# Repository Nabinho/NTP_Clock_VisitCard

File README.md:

# NTP_Clock_VisitCard

Linkit 7697 based NTP Digital Clock with a Visti Card PCB

I have the idea of creating an Visit Card to promote myself as a Software and Hardware Developer and project consultant, and for that I decided to go with a PCB in the format of a Credit Card. The circuit chosen is a project I always wanted to build, as I don´t have clocks due to the time to time need for manual calibration. So I connected the LinkIt 7697 (unfortunately discontinued) I had available, to connect it to a NTP server, and be always up to time. The board then controls 4 7-digits displays by 4 4511 ICs that are indirectly driven by ULN2003 transistors.

If you are interested in building your own Visit Card based on this project, feel free to change the PCB file with your own information. Just remember to give some credit.

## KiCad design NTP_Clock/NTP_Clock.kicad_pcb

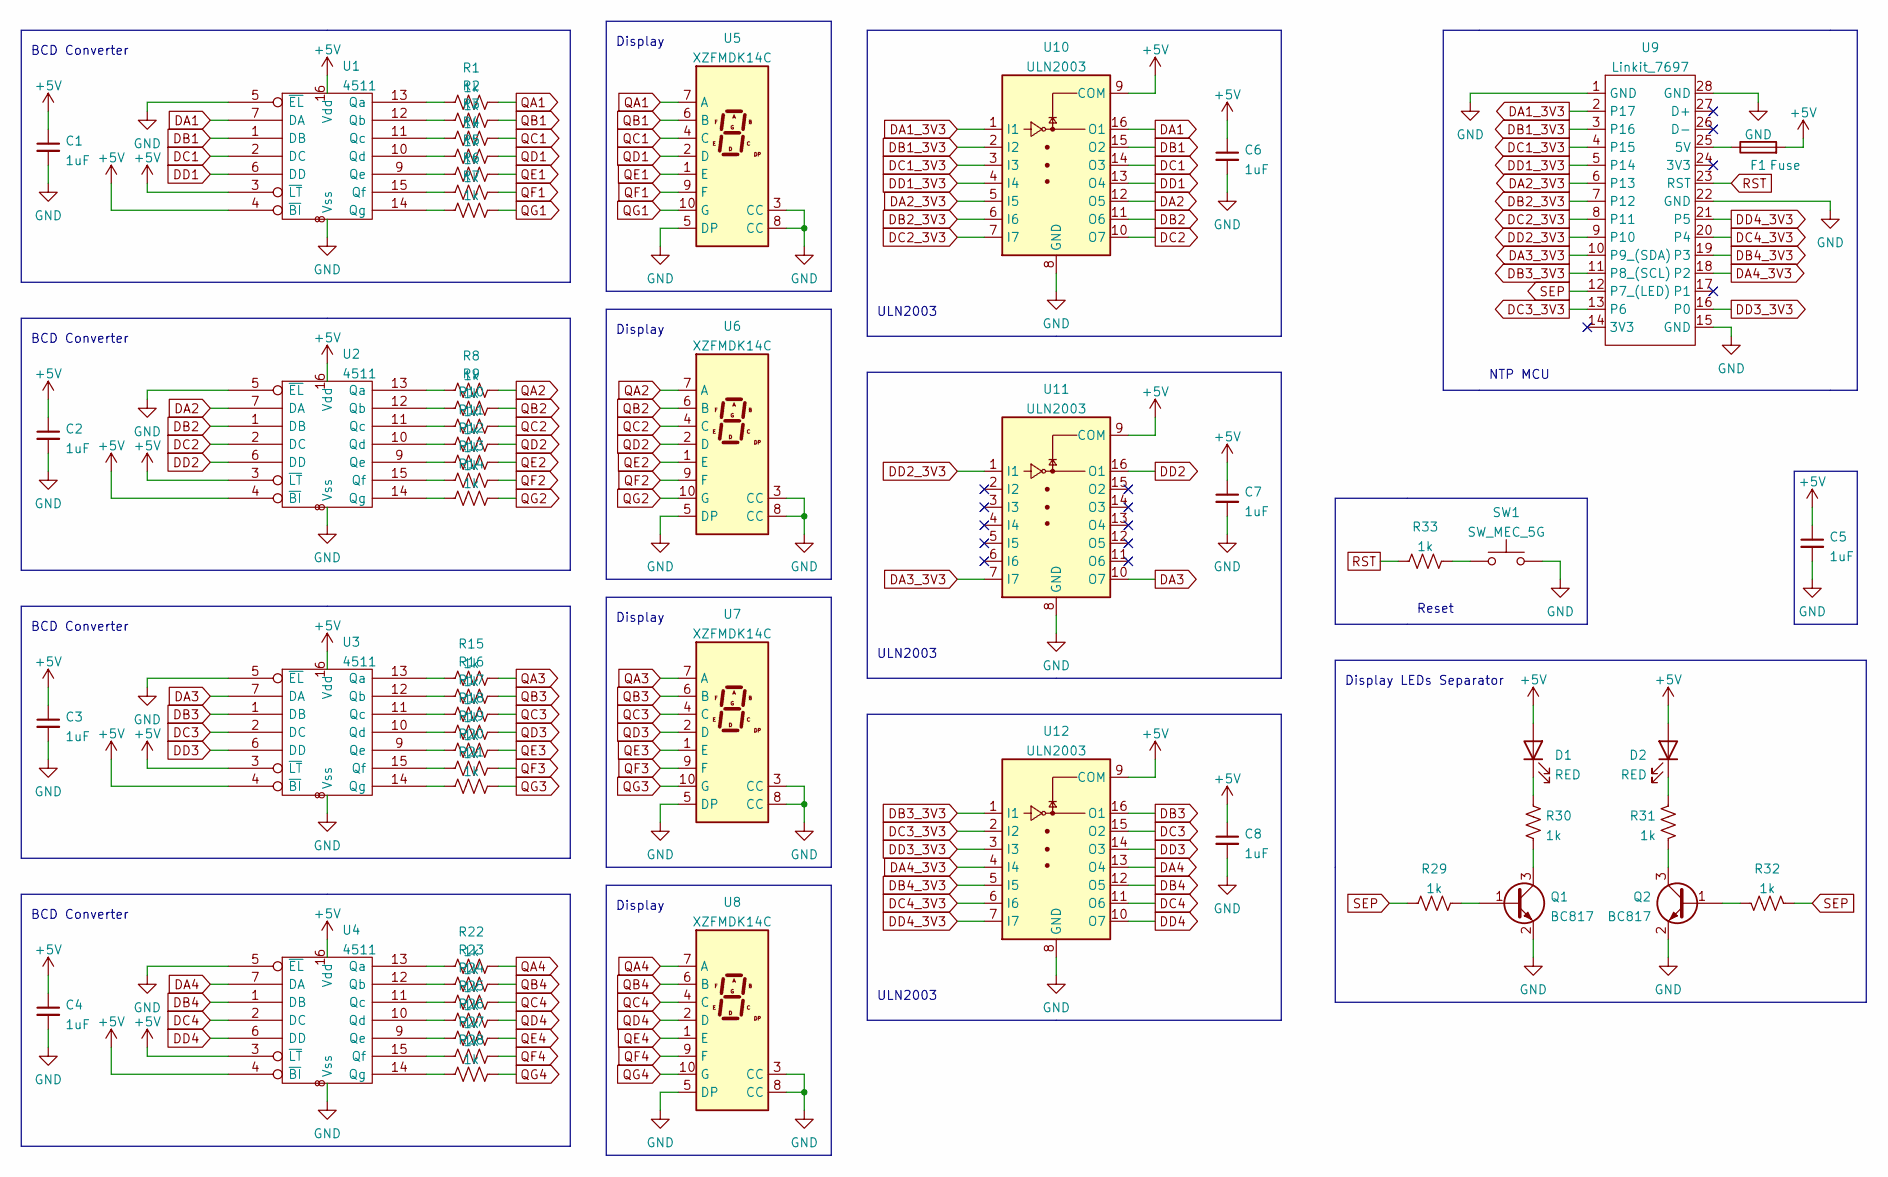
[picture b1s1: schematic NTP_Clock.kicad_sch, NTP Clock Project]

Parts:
C1, C2, C3, C4, C5, C6, C7, C8: 1uF; C_0805_2012Metric
D1, D2: RED; LED_0805_2012Metric
F1: Fuse; Fuse_0805_2012Metric
Q1, Q2: BC817; SOT-23
R1, R2, R3, R4, R5, R6, R7, R8, R9, R10, R11, R12, R13, R14, R15, R16, R17, R18, R19, R20, R21, R22, R23, R24, R25, R26, R27, R28, R29, R30, R31, R32, R33: 1k; R_0805_2012Metric
SW1: SW_MEC_5G; SW_SPST_SKQG_WithStem
U1, U2, U3, U4: 4511; SO-16_5.3x10.2mm_P1.27mm
U5, U6, U7, U8: XZFMDK14C; 7SEGMENT-LED__HDSM531_HDSM533_SMD
U9: Linkit_7697; Linkit
U10, U11, U12: ULN2003; SO-16_5.3x10.2mm_P1.27mm

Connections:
+5V: C1.1, C2.1, C3.1, C4.1, C5.1, C6.1, C7.1, C8.1, D1.2 (A), D2.2 (A), F1.2, U1.3 (~LT), U1.4 (~BI), U1.16 (Vdd), U2.3 (~LT), U2.4 (~BI), U2.16 (Vdd), U3.3 (~LT), U3.4 (~BI), U3.16 (Vdd), U4.3 (~LT), U4.4 (~BI), U4.16 (Vdd), U10.9 (COM), U11.9 (COM), U12.9 (COM)
DA1: U1.7 (DA), U10.16 (O1)
DA1_3V3: U9.2 (P17), U10.1 (I1)
DA2: U2.7 (DA), U10.12 (O5)
DA2_3V3: U9.6 (P13), U10.5 (I5)
DA3: U3.7 (DA), U11.10 (O7)
DA3_3V3: U9.10 (P9_(SDA)), U11.7 (I7)
DA4: U4.7 (DA), U12.13 (O4)
DA4_3V3: U9.18 (P2), U12.4 (I4)
DB1: U1.1 (DB), U10.15 (O2)
DB1_3V3: U9.3 (P16), U10.2 (I2)
DB2: U2.1 (DB), U10.11 (O6)
DB2_3V3: U9.7 (P12), U10.6 (I6)
DB3: U3.1 (DB), U12.16 (O1)
DB3_3V3: U9.11 (P8_(SCL)), U12.1 (I1)
DB4: U4.1 (DB), U12.12 (O5)
DB4_3V3: U9.19 (P3), U12.5 (I5)
DC1: U1.2 (DC), U10.14 (O3)
DC1_3V3: U9.4 (P15), U10.3 (I3)
DC2: U2.2 (DC), U10.10 (O7)
DC2_3V3: U9.8 (P11), U10.7 (I7)
DC3: U3.2 (DC), U12.15 (O2)
DC3_3V3: U9.13 (P6), U12.2 (I2)
DC4: U4.2 (DC), U12.11 (O6)
DC4_3V3: U9.20 (P4), U12.6 (I6)
DD1: U1.6 (DD), U10.13 (O4)
DD1_3V3: U9.5 (P14), U10.4 (I4)
DD2: U2.6 (DD), U11.16 (O1)
DD2_3V3: U9.9 (P10), U11.1 (I1)
DD3: U3.6 (DD), U12.14 (O3)
DD3_3V3: U9.16 (P0), U12.3 (I3)
DD4: U4.6 (DD), U12.10 (O7)
DD4_3V3: U9.21 (P5), U12.7 (I7)
unnamed: D1.1 (K), R30.2
unnamed: D2.1 (K), R31.2
unnamed: F1.1, U9.25 (5V)
unnamed: Q1.1 (B), R29.2
unnamed: Q1.3 (C), R30.1
unnamed: Q2.1 (B), R32.2
unnamed: Q2.3 (C), R31.1
unnamed: R1.1, U1.13 (Qa)
unnamed: R2.1, U1.12 (Qb)
unnamed: R3.1, U1.11 (Qc)
unnamed: R4.1, U1.10 (Qd)
unnamed: R5.1, U1.9 (Qe)
unnamed: R6.1, U1.15 (Qf)
unnamed: R7.1, U1.14 (Qg)
unnamed: R8.1, U2.13 (Qa)
unnamed: R9.1, U2.12 (Qb)
unnamed: R10.1, U2.11 (Qc)
unnamed: R11.1, U2.10 (Qd)
unnamed: R12.1, U2.9 (Qe)
unnamed: R13.1, U2.15 (Qf)
unnamed: R14.1, U2.14 (Qg)
unnamed: R15.1, U3.13 (Qa)
unnamed: R16.1, U3.12 (Qb)
unnamed: R17.1, U3.11 (Qc)
unnamed: R18.1, U3.10 (Qd)
unnamed: R19.1, U3.9 (Qe)
unnamed: R20.1, U3.15 (Qf)
unnamed: R21.1, U3.14 (Qg)
unnamed: R22.1, U4.13 (Qa)
unnamed: R23.1, U4.12 (Qb)
unnamed: R24.1, U4.11 (Qc)
unnamed: R25.1, U4.10 (Qd)
unnamed: R26.1, U4.9 (Qe)
unnamed: R27.1, U4.15 (Qf)
unnamed: R28.1, U4.14 (Qg)
QA1: R1.2, U5.7 (A)
QA2: R8.2, U6.7 (A)
QA3: R15.2, U7.7 (A)
QA4: R22.2, U8.7 (A)
QB1: R2.2, U5.6 (B)
QB2: R9.2, U6.6 (B)
QB3: R16.2, U7.6 (B)
QB4: R23.2, U8.6 (B)
QC1: R3.2, U5.4 (C)
QC2: R10.2, U6.4 (C)
QC3: R17.2, U7.4 (C)
QC4: R24.2, U8.4 (C)
QD1: R4.2, U5.2 (D)
QD2: R11.2, U6.2 (D)
QD3: R18.2, U7.2 (D)
QD4: R25.2, U8.2 (D)
QE1: R5.2, U5.1 (E)
QE2: R12.2, U6.1 (E)
QE3: R19.2, U7.1 (E)
QE4: R26.2, U8.1 (E)
QF1: R6.2, U5.9 (F)
QF2: R13.2, U6.9 (F)
QF3: R20.2, U7.9 (F)
QF4: R27.2, U8.9 (F)
QG1: R7.2, U5.10 (G)
QG2: R14.2, U6.10 (G)
QG3: R21.2, U7.10 (G)
QG4: R28.2, U8.10 (G)
RST: R33.1, U9.23 (RST)
SEP: R29.1, R32.1, U9.12 (P7_(LED))

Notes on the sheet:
ULN2003
Display
Reset
BCD Converter
NTP MCU
Display LEDs Separator

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
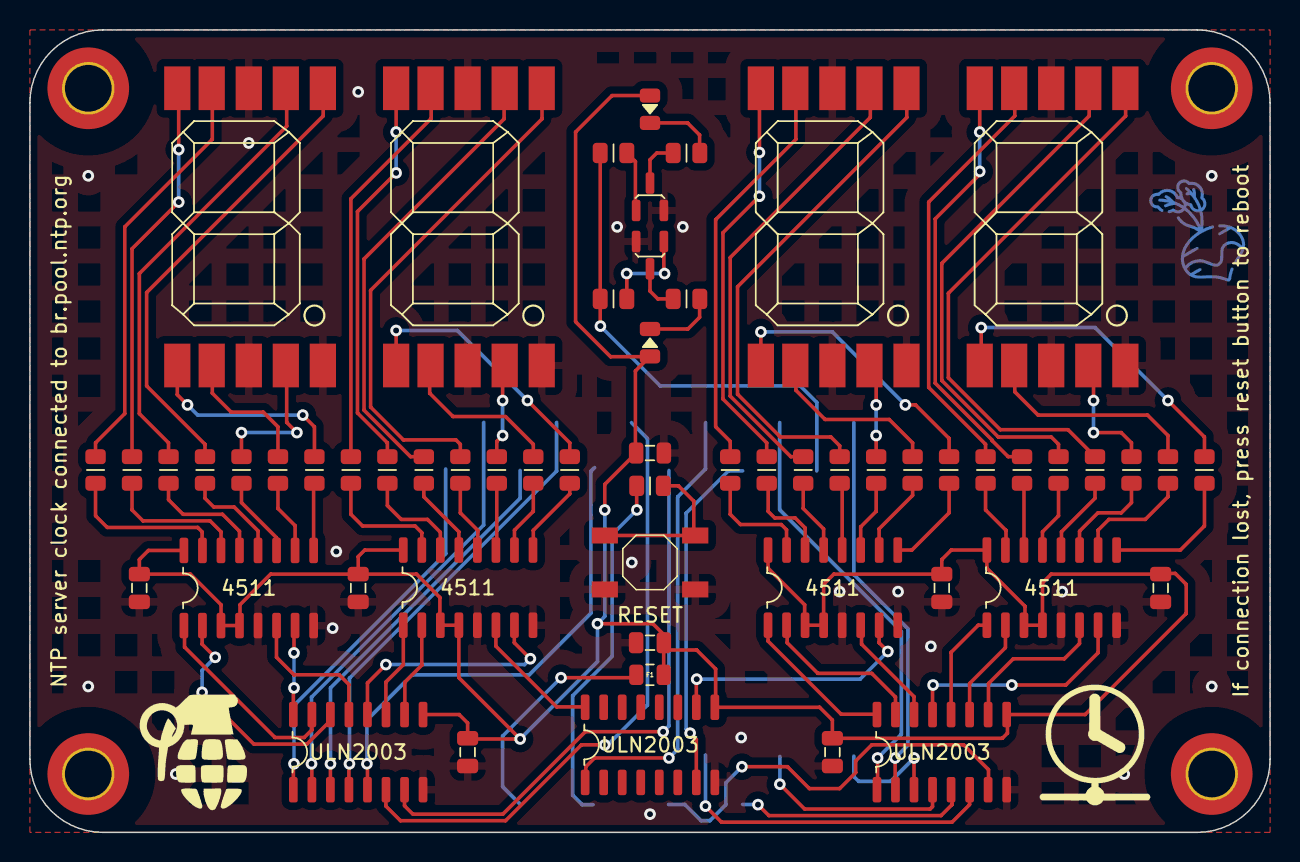
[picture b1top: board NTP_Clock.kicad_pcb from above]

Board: 2 copper layers, 85.0 x 55.0 mm, 59 parts (1 on the bottom side), 100 nets.

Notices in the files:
NTP_Clock/NTP_Clock.kicad_sch:
Creative Commons Attribution Share-Alike 4.0 License
